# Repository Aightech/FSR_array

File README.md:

# FSR_array

This project implements a electronic skin using a FSR accelerometers arrays. 

The electronic board uses two multiplexers and two 16-channel ADCs to read the FSRs. The multiplexers are used to select the row or column of the FSRs array. The ADCs are used to read the FSRs values.
A teensy 4.1 is used to control the multiplexers and ADCs and to send the data to the computer.
The teensy 4.1 is connected to the computer using a USB cable or ethernet cable.
There are two modes of operation:
- **Single mode**: In this mode, you can connect a FSR array with up to 32x32 FSRs.
- **Dual mode**: In this mode, you can connect two FSR arrays with up to 16x16 FSRs each.

The sampling is around 400KHz/channel. So for a 16x16 FSR array, the sampling rate is around 400KHz/256 = 1562.5Hz.

The project contains a C++/matlab/python code demonstrating how to communicate with the teensy 4.1 and read the FSRs values.

### Submodules dependencies
#### libraries
- [built_lsl](lib/built_lsl/README.md)
- [com_client](lib/com_client/README.md)

# Building source code

To build the project run:
```bash
cd FSR_array
mkdir build && cd build
cmake .. && make
```

# Demonstration app

When the project have been built, you can run:
```bash
./FSR_array -h
```
to get the demonstration app usage.

# Example
Open the  file to get an example how to use the lib.

# Contributing
See [CONTRIBUTING.md](CONTRIBUTING.md) for details on our code of conduct, and the process for submitting pull requests to us.

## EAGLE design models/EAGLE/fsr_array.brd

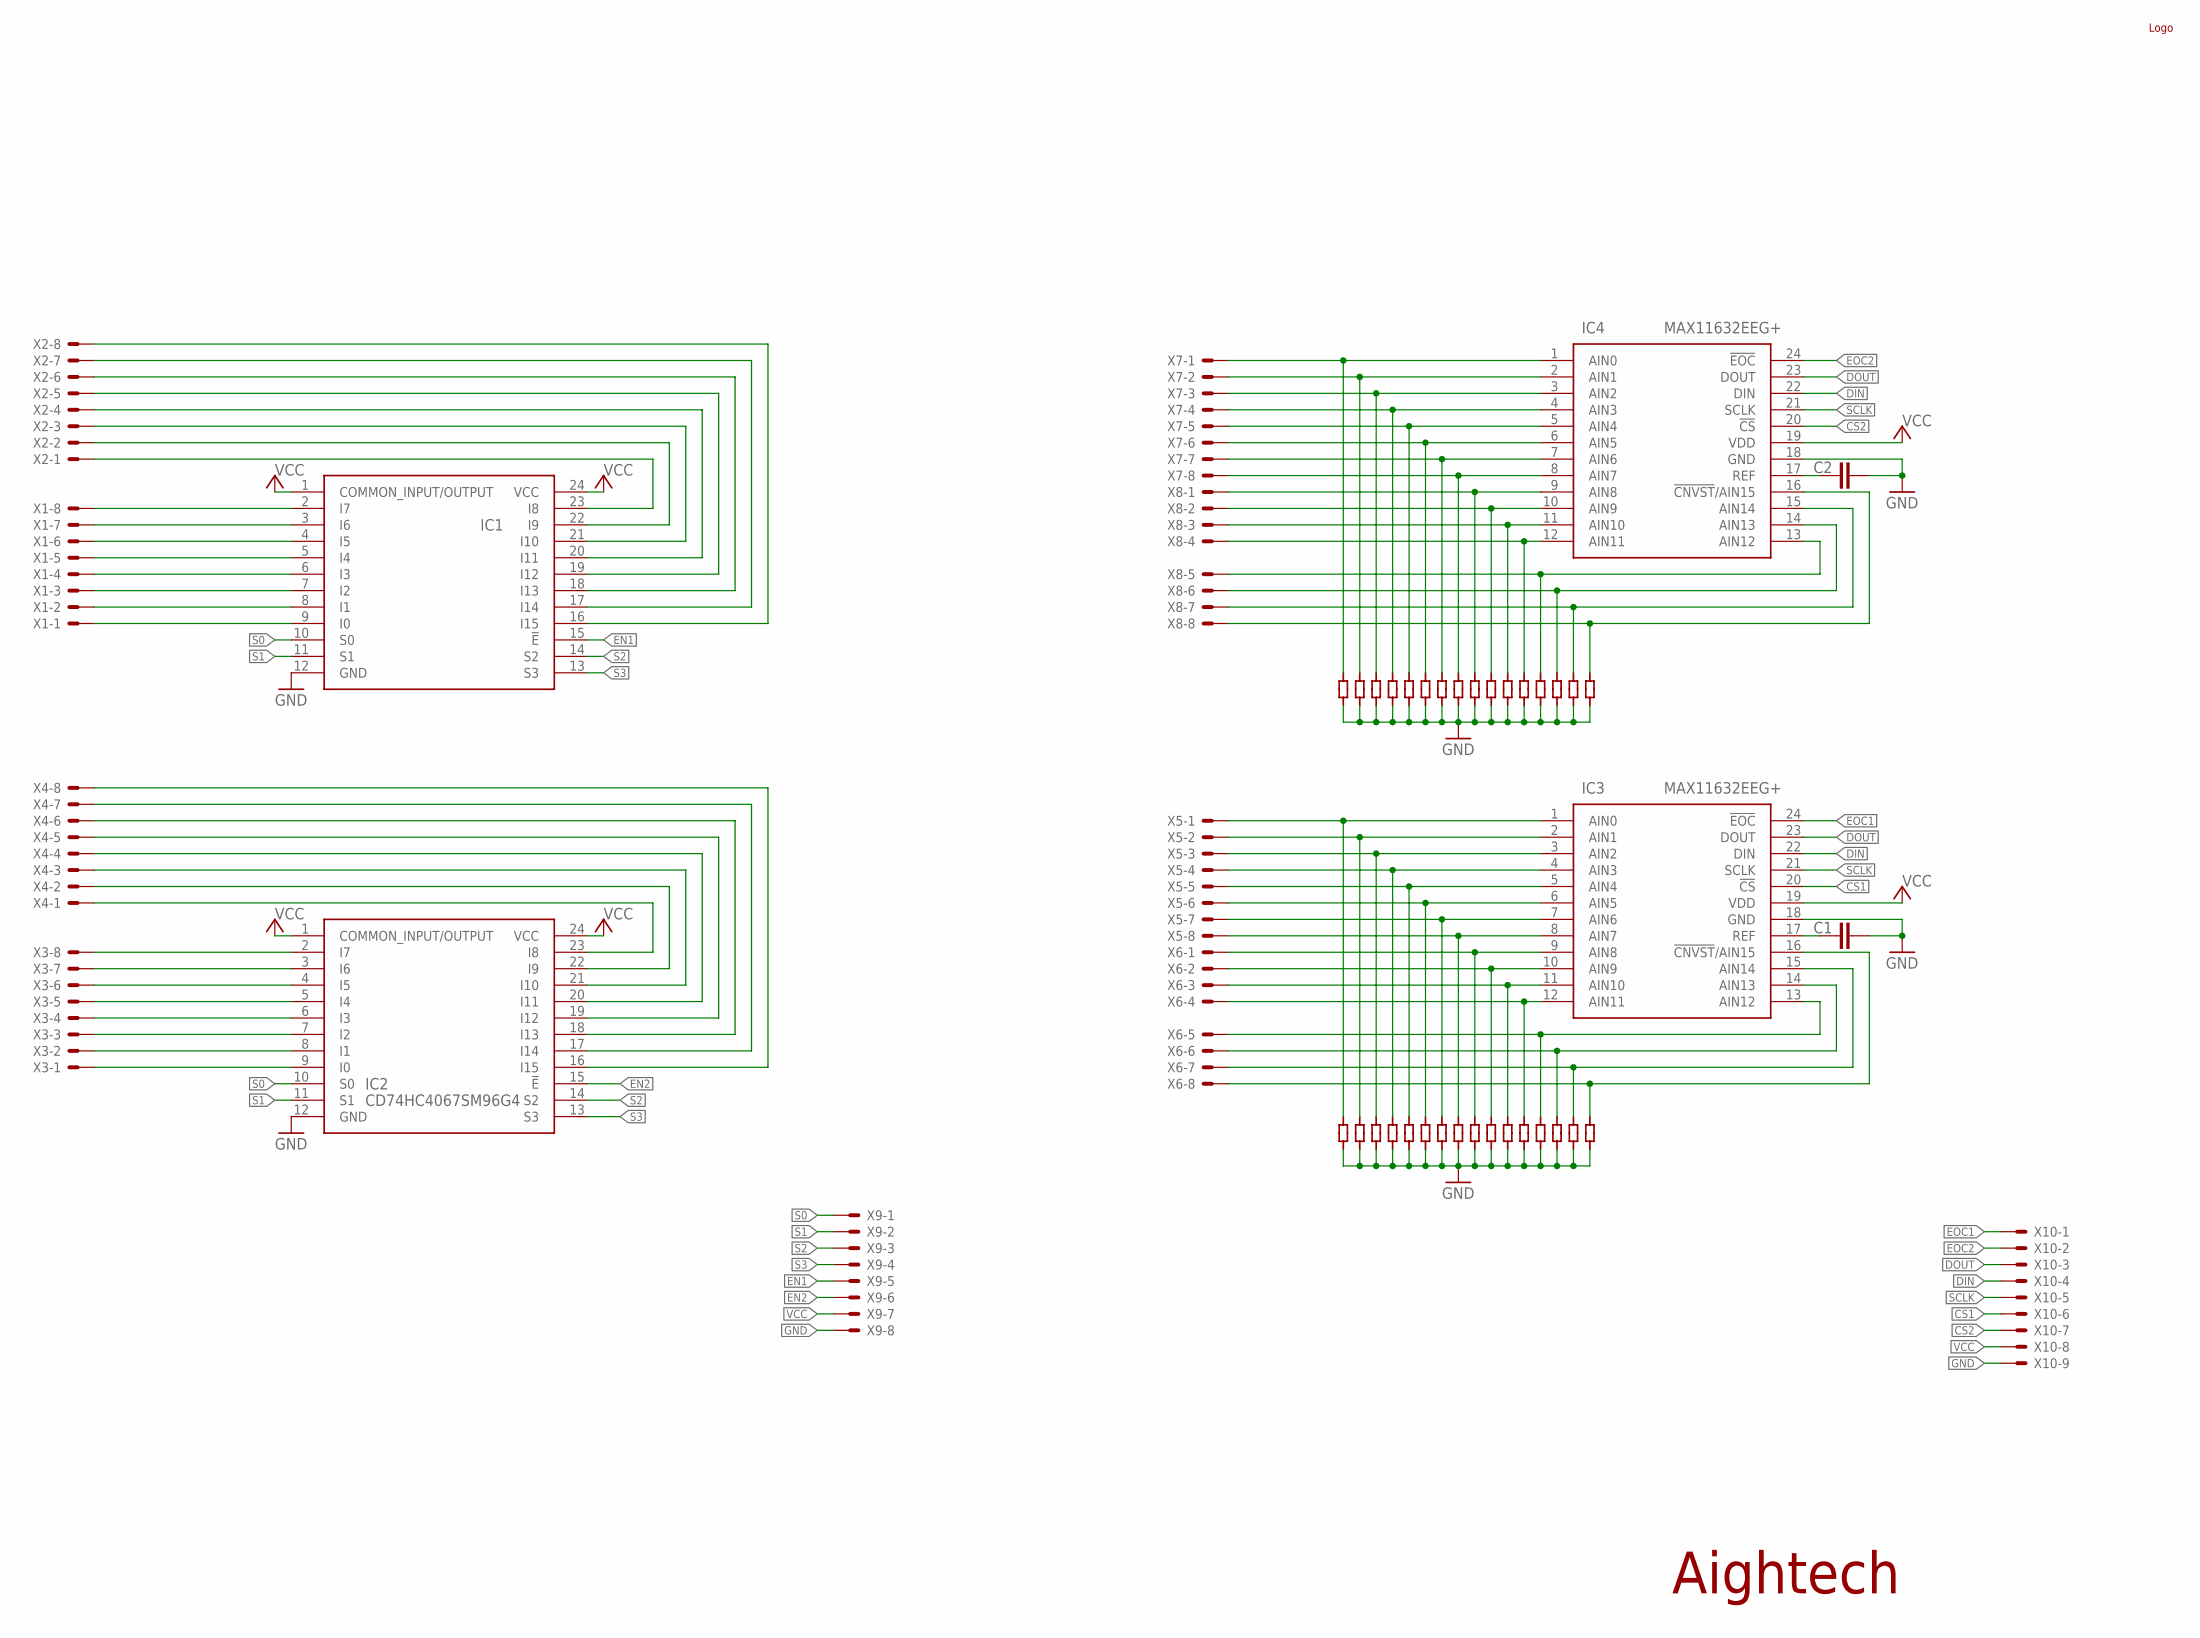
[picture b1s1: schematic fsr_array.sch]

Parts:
C1, C2: C-EUC0603; C0603
CPLX1: LOGO
IC1, IC2: CD74HC4067SM96G4; SOP65P780X200-24N
IC3, IC4: MAX11632EEG+; SOP64P602X175-24N
U$1, U$2, U$3, U$4, U$5, U$6, U$7, U$8, U$9, U$10, U$11, U$12, U$13, U$14, U$15, U$16, U$17, U$18, U$19, U$20, U$21, U$22, U$23, U$24, U$25, U$26, U$27, U$28, U$29, U$30, U$31, U$32, U$33, U$34, U$35, U$36, U$37, U$38, U$39, U$40, U$41, U$42, U$43, U$44, U$45, U$46, U$47, U$48, U$49, U$50, U$51, U$52, U$53, U$54, U$55, U$56, U$57, U$58, U$59, U$60, U$61, U$62, U$63, U$64: HALF_RES; HALP_RES
X1, X2, X3, X4, X5, X6, X7, X8, X9: 22-23-2081
X10: 22-23-2091

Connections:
CS1: IC3.20 (!CS), X10.6
CS2: IC4.20 (!CS), X10.7
DIN: IC3.22 (DIN), IC4.22 (DIN), X10.4
DOUT: IC3.23 (DOUT), IC4.23 (DOUT), X10.3
EN1: IC1.15 (!E), X9.5
EN2: IC2.15 (!E), X9.6
EOC1: IC3.24 (!EOC), X10.1
EOC2: IC4.24 (!EOC), X10.2
GND: C1.2, C2.2, IC1.12 (GND), IC2.12 (GND), IC3.18 (GND), IC4.18 (GND), U$1.P$1, U$3.P$1, U$5.P$1, U$7.P$1, U$9.P$1, U$11.P$1, U$13.P$1, U$15.P$1, U$17.P$1, U$19.P$1, U$21.P$1, U$23.P$1, U$25.P$1, U$27.P$1, U$29.P$1, U$31.P$1, U$33.P$1, U$35.P$1, U$37.P$1, U$39.P$1, U$41.P$1, U$43.P$1, U$45.P$1, U$47.P$1, U$49.P$1, U$51.P$1, U$53.P$1, U$55.P$1, U$57.P$1, U$59.P$1, U$61.P$1, U$63.P$1, X9.8, X10.9
unnamed: IC1.9 (I0), X1.1
unnamed: IC1.8 (I1), X1.2
unnamed: IC1.7 (I2), X1.3
unnamed: IC1.6 (I3), X1.4
unnamed: IC1.5 (I4), X1.5
unnamed: IC1.4 (I5), X1.6
unnamed: IC1.3 (I6), X1.7
unnamed: IC1.2 (I7), X1.8
unnamed: IC1.23 (I8), X2.1
unnamed: IC1.22 (I9), X2.2
unnamed: IC1.21 (I10), X2.3
unnamed: IC1.20 (I11), X2.4
unnamed: IC1.19 (I12), X2.5
unnamed: IC1.18 (I13), X2.6
unnamed: IC1.17 (I14), X2.7
unnamed: IC1.16 (I15), X2.8
unnamed: IC2.9 (I0), X3.1
unnamed: IC2.8 (I1), X3.2
unnamed: IC2.7 (I2), X3.3
unnamed: IC2.6 (I3), X3.4
unnamed: IC2.5 (I4), X3.5
unnamed: IC2.4 (I5), X3.6
unnamed: IC2.3 (I6), X3.7
unnamed: IC2.2 (I7), X3.8
unnamed: IC2.23 (I8), X4.1
unnamed: IC2.22 (I9), X4.2
unnamed: IC2.21 (I10), X4.3
unnamed: IC2.20 (I11), X4.4
unnamed: IC2.19 (I12), X4.5
unnamed: IC2.18 (I13), X4.6
unnamed: IC2.17 (I14), X4.7
unnamed: IC2.16 (I15), X4.8
unnamed: IC3.1 (AIN0), U$16.P$1, X5.1
unnamed: IC3.2 (AIN1), U$14.P$1, X5.2
unnamed: IC3.3 (AIN2), U$12.P$1, X5.3
unnamed: IC3.4 (AIN3), U$10.P$1, X5.4
unnamed: IC3.5 (AIN4), U$8.P$1, X5.5
unnamed: IC3.6 (AIN5), U$6.P$1, X5.6
unnamed: IC3.7 (AIN6), U$4.P$1, X5.7
unnamed: IC3.8 (AIN7), U$2.P$1, X5.8
unnamed: IC3.9 (AIN8), U$32.P$1, X6.1
unnamed: IC3.10 (AIN9), U$30.P$1, X6.2
unnamed: IC3.11 (AIN10), U$28.P$1, X6.3
unnamed: IC3.12 (AIN11), U$26.P$1, X6.4
unnamed: IC3.13 (AIN12), U$24.P$1, X6.5
unnamed: IC3.14 (AIN13), U$22.P$1, X6.6
unnamed: IC3.15 (AIN14), U$20.P$1, X6.7
unnamed: IC3.16 (!CNVST!/AIN15), U$18.P$1, X6.8
unnamed: IC4.1 (AIN0), U$48.P$1, X7.1
unnamed: IC4.2 (AIN1), U$46.P$1, X7.2
unnamed: IC4.3 (AIN2), U$44.P$1, X7.3
unnamed: IC4.4 (AIN3), U$42.P$1, X7.4
unnamed: IC4.5 (AIN4), U$40.P$1, X7.5
unnamed: IC4.6 (AIN5), U$38.P$1, X7.6
unnamed: IC4.7 (AIN6), U$36.P$1, X7.7
unnamed: IC4.8 (AIN7), U$34.P$1, X7.8
unnamed: IC4.9 (AIN8), U$64.P$1, X8.1
unnamed: IC4.10 (AIN9), U$62.P$1, X8.2
unnamed: IC4.11 (AIN10), U$60.P$1, X8.3
unnamed: IC4.12 (AIN11), U$58.P$1, X8.4
unnamed: IC4.13 (AIN12), U$56.P$1, X8.5
unnamed: IC4.14 (AIN13), U$54.P$1, X8.6
unnamed: IC4.15 (AIN14), U$52.P$1, X8.7
unnamed: IC4.16 (!CNVST!/AIN15), U$50.P$1, X8.8
unnamed: C1.1, IC3.17 (REF)
unnamed: C2.1, IC4.17 (REF)
S0: IC1.10 (S0), IC2.10 (S0), X9.1
S1: IC1.11 (S1), IC2.11 (S1), X9.2
S2: IC1.14 (S2), IC2.14 (S2), X9.3
S3: IC1.13 (S3), IC2.13 (S3), X9.4
SCLK: IC3.21 (SCLK), IC4.21 (SCLK), X10.5
VCC: IC1.1 (COMMON_INPUT/OUTPUT), IC1.24 (VCC), IC2.1 (COMMON_INPUT/OUTPUT), IC2.24 (VCC), IC3.19 (VDD), IC4.19 (VDD), X9.7, X10.8

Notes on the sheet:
Aightech

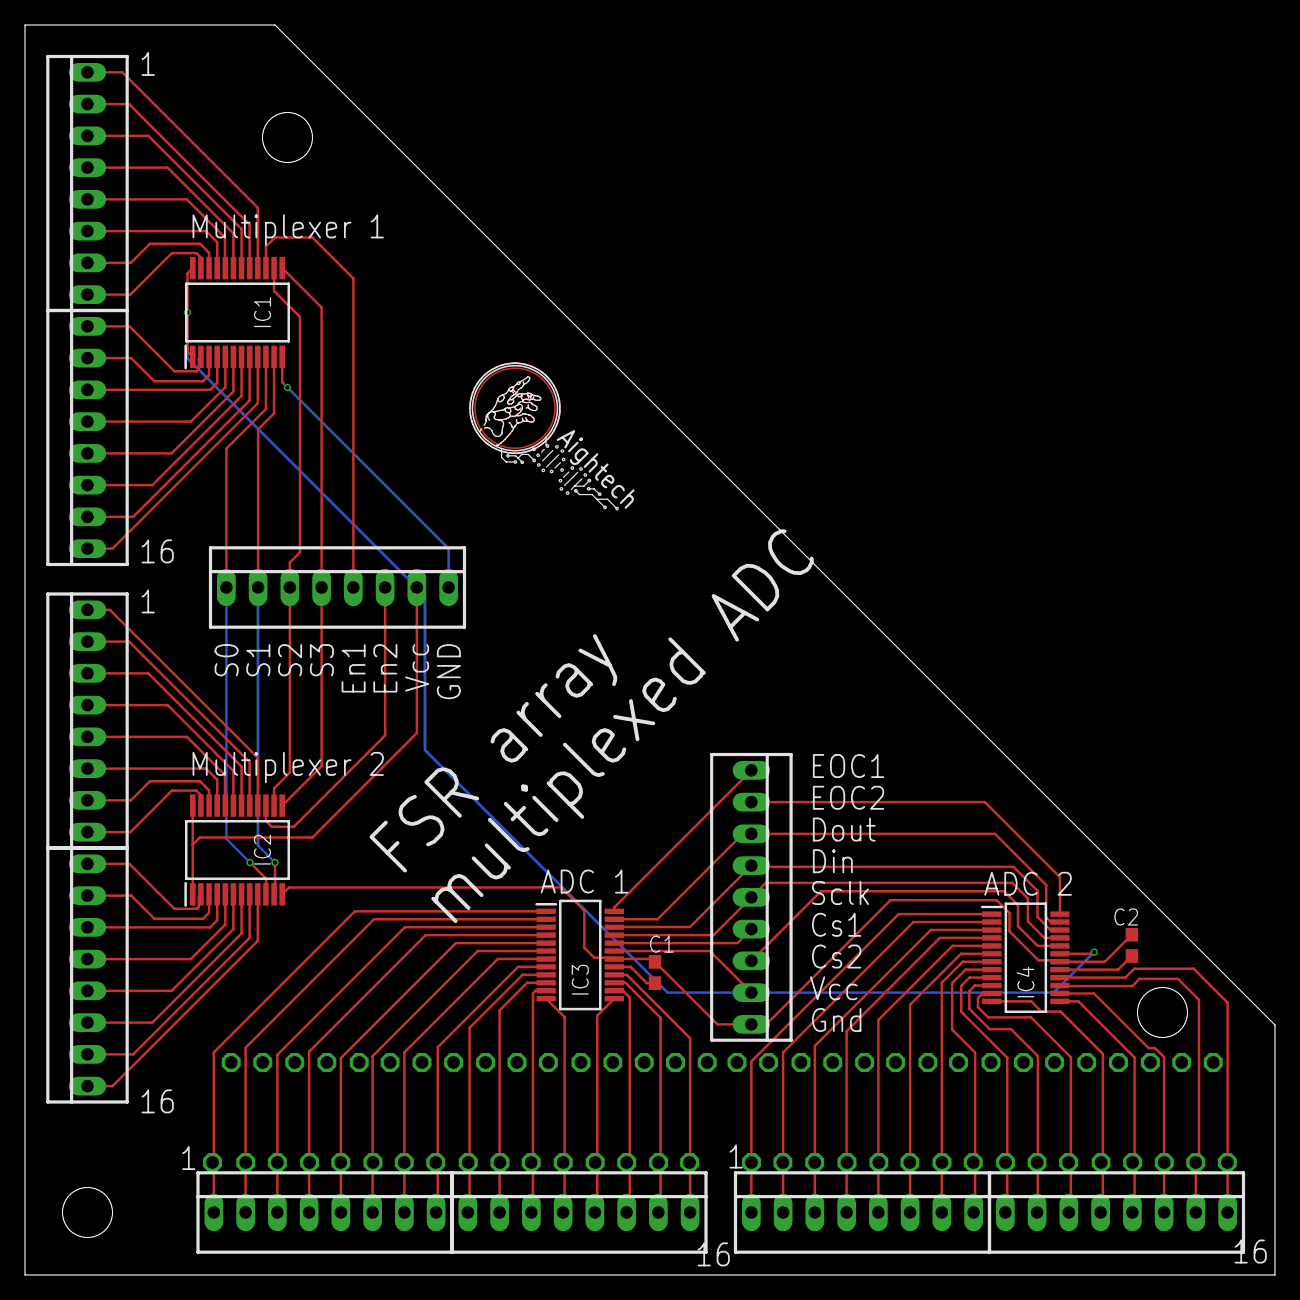
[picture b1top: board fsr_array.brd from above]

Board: 2 copper layers, 100.0 x 100.0 mm, 81 parts (0 on the bottom side), 81 nets.

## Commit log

2022-07-01 added board
2022-07-01 added datasheets
2022-07-01 Solidwork model
2022-08-29 added matlab script
2022-08-29 updated the python script to record with timestamps
2022-08-29 fixed closing issue of the serial port in the record.py script
2022-08-29 n can be set via command arg
2022-08-31 letters models
2022-09-13 big_letters
2022-09-14 update big letters
2022-09-14 update on letters
2022-10-25 v3 kicad
2022-11-11 v2 pcbboard and comments on matlab script
2023-05-25 working step for the cpp lsl publisher
2023-05-28 Create FSR support
2023-07-17 fixed minor bug + added ethernet teensy code
2023-08-14 updated LIS3DH array
2024-03-16 updated lis3dh array: fpc connectors
2024-07-18 added LIS2DH version with or gate to solve SPI/i2C interaction
2024-07-20 working code for the accelerometers + FSRs
2024-08-31 added or gate on each acc to prevent I2C interference when the chip have CSB high
2024-09-01 updated lis2dh arrays
2024-09-29 new custom fsr model
2024-10-04 modify the fixation position to fit better on finger
2024-10-21 added teeardrops
2024-10-23 added scripts for customFSR
2025-02-27 starting tear drops
